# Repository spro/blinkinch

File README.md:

# blinkinch

Square inch clone of the blink(1) indicator light with ATTiny85 and V-USB.

Created to participate in the [Square Inch Project](https://hackaday.io/project/7813-the-square-inch-project). The design goal was to make something somewhat useful (a programmable indicator light) that is very easy to reproduce (with minimal, common, through-hole parts).

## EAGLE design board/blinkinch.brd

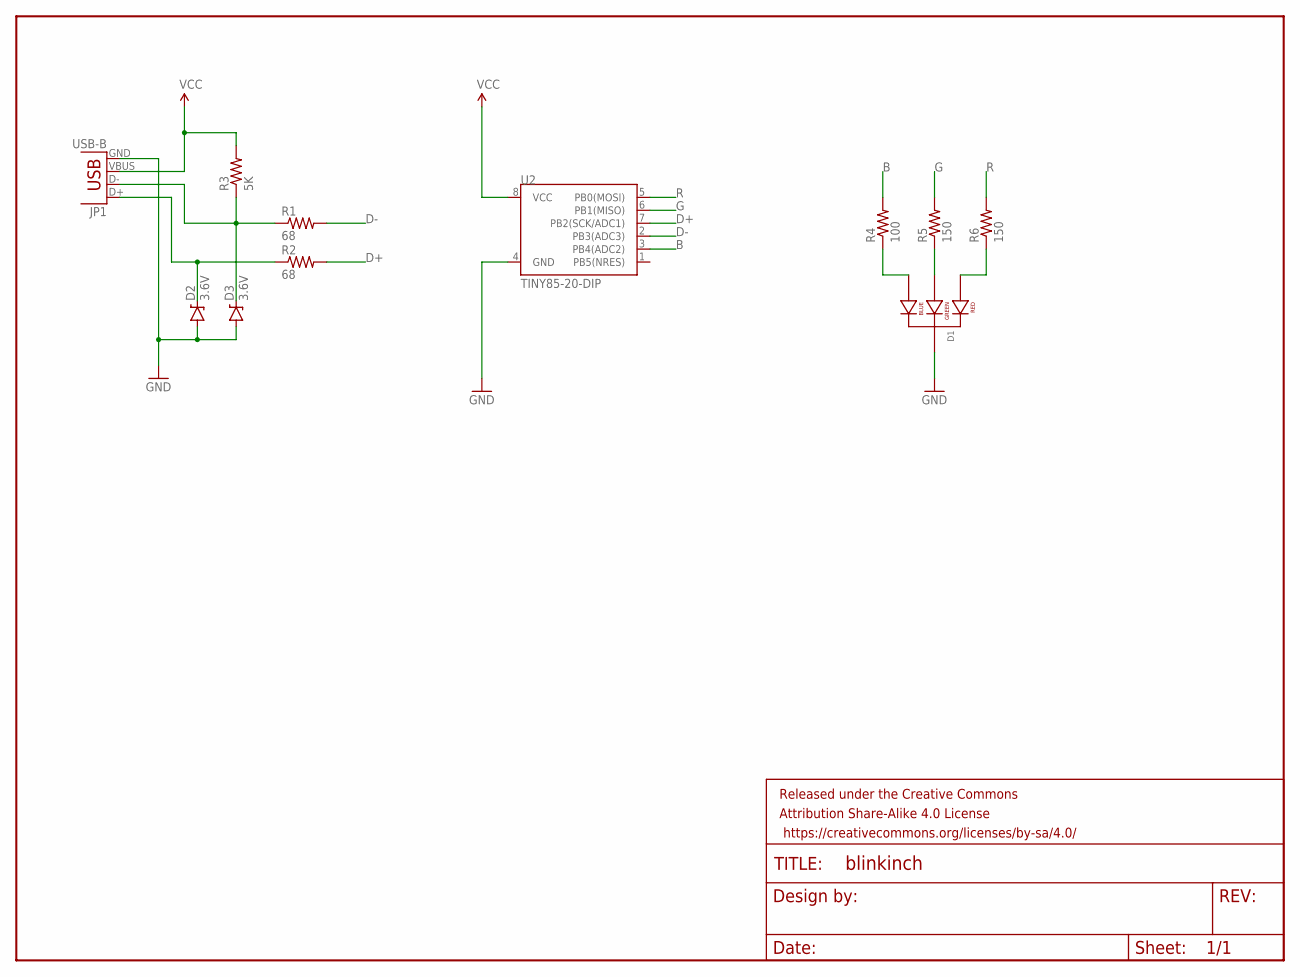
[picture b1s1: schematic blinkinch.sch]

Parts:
D1: LED-RGB-CC-THRUCLEAR; LED-RGB-THRU
D2, D3: 3.6V; DIODE-ZENER
FRAME1: FRAME-LETTER; CREATIVE_COMMONS
JP1: USB-B; USB-B-PTH
R1, R2: 68; AXIAL-0.1
R3: 5K; AXIAL-0.1
R4: 100; AXIAL-0.1
R5, R6: 150; AXIAL-0.1
U2: TINY85-20-DIP; DIP08

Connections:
B: R4.P$2 (2), U2.3 (PB4(ADC2))
D+: R2.P$2 (2), U2.7 (PB2(SCK/ADC1))
D-: R1.P$2 (2), U2.2 (PB3(ADC3))
G: R5.P$2 (2), U2.6 (PB1(MISO))
GND: D1.2 (CATHODE), D2.P$2 (A), D3.P$2 (A), JP1.GND, U2.4 (GND)
unnamed: D1.4 (BLUE_CATHODE), R4.P$1 (1)
unnamed: D1.3 (GREEN_CATHODE), R5.P$1 (1)
unnamed: D1.1 (RED_CATHODE), R6.P$1 (1)
unnamed: D3.P$1 (C), JP1.D-, R1.P$1 (1), R3.P$1 (1)
unnamed: D2.P$1 (C), JP1.D+, R2.P$1 (1)
R: R6.P$2 (2), U2.5 (PB0(MOSI))
VCC: JP1.VBUS, R3.P$2 (2), U2.8 (VCC)

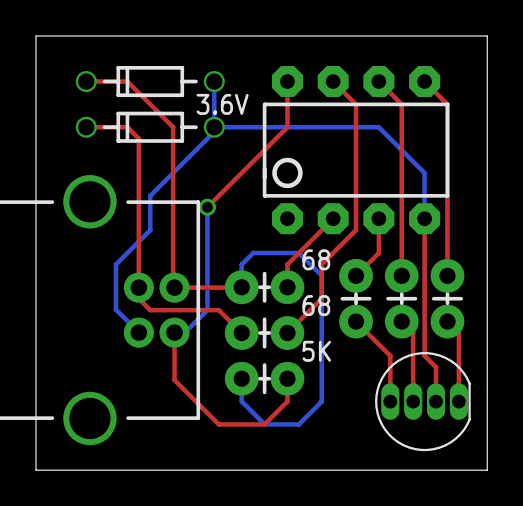
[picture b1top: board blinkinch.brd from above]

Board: 2 copper layers, 25.1 x 24.1 mm, 12 parts (0 on the bottom side), 12 nets.

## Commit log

2015-12-02 add screenshot
2015-12-11 openscad enclosure
2015-12-11 more pictures
2016-01-10 add python driver
2016-01-10 usage and api sections in readme
2019-05-29 add blinkinch firmware
2019-06-04 Added build instructions.

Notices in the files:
parts and their libraries:
SparkFun-LED: Licensing: Creative Commons ShareAlike 4.0 International - https://creativecommons.org/licenses/by-sa/4.0
SparkFun-Aesthetics: Released under the Creative Commons Attribution Share-Alike 4.0 License
SparkFun-Aesthetics: https://creativecommons.org/licenses/by-sa/4.0
